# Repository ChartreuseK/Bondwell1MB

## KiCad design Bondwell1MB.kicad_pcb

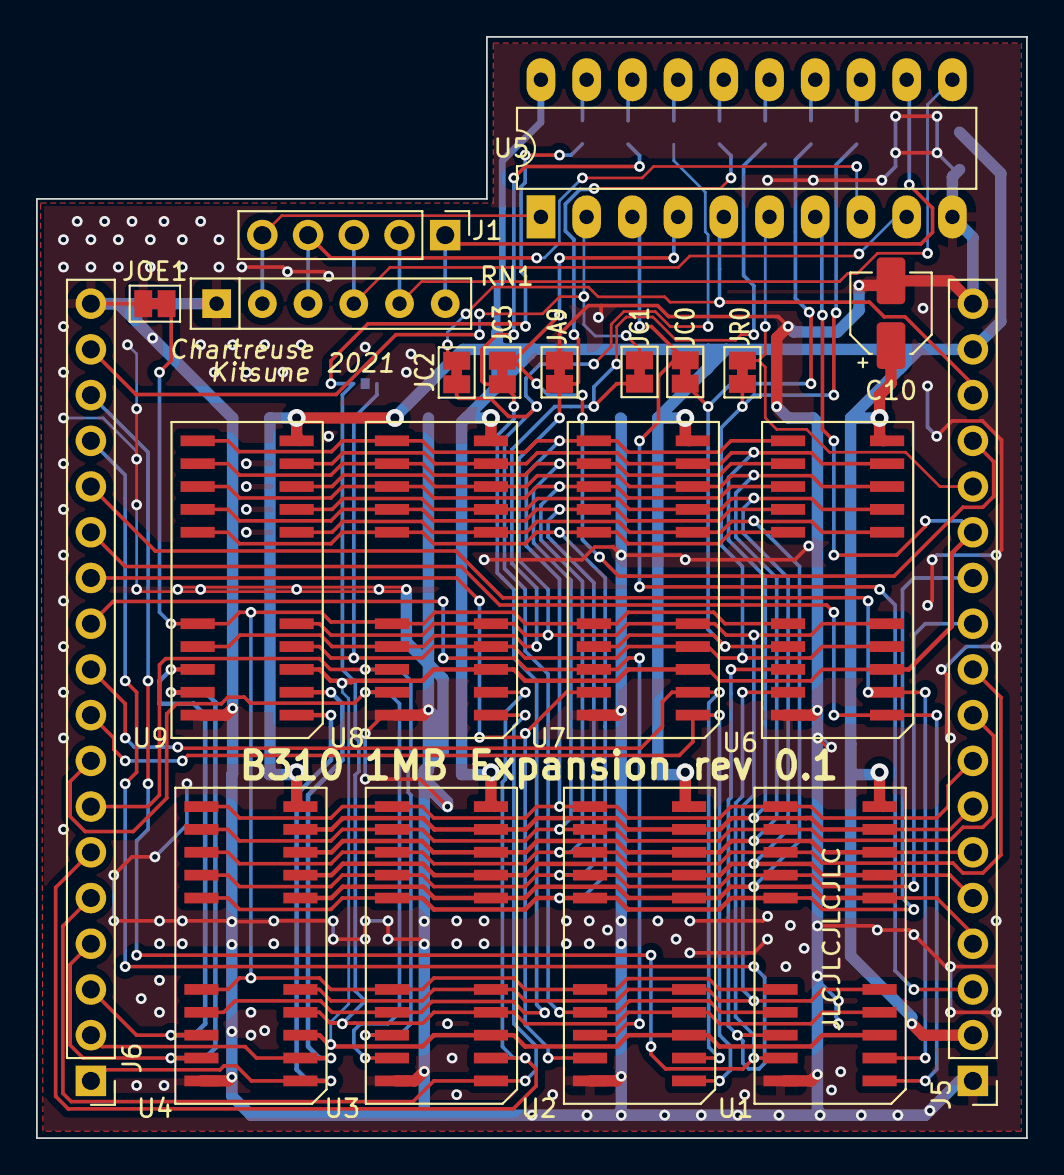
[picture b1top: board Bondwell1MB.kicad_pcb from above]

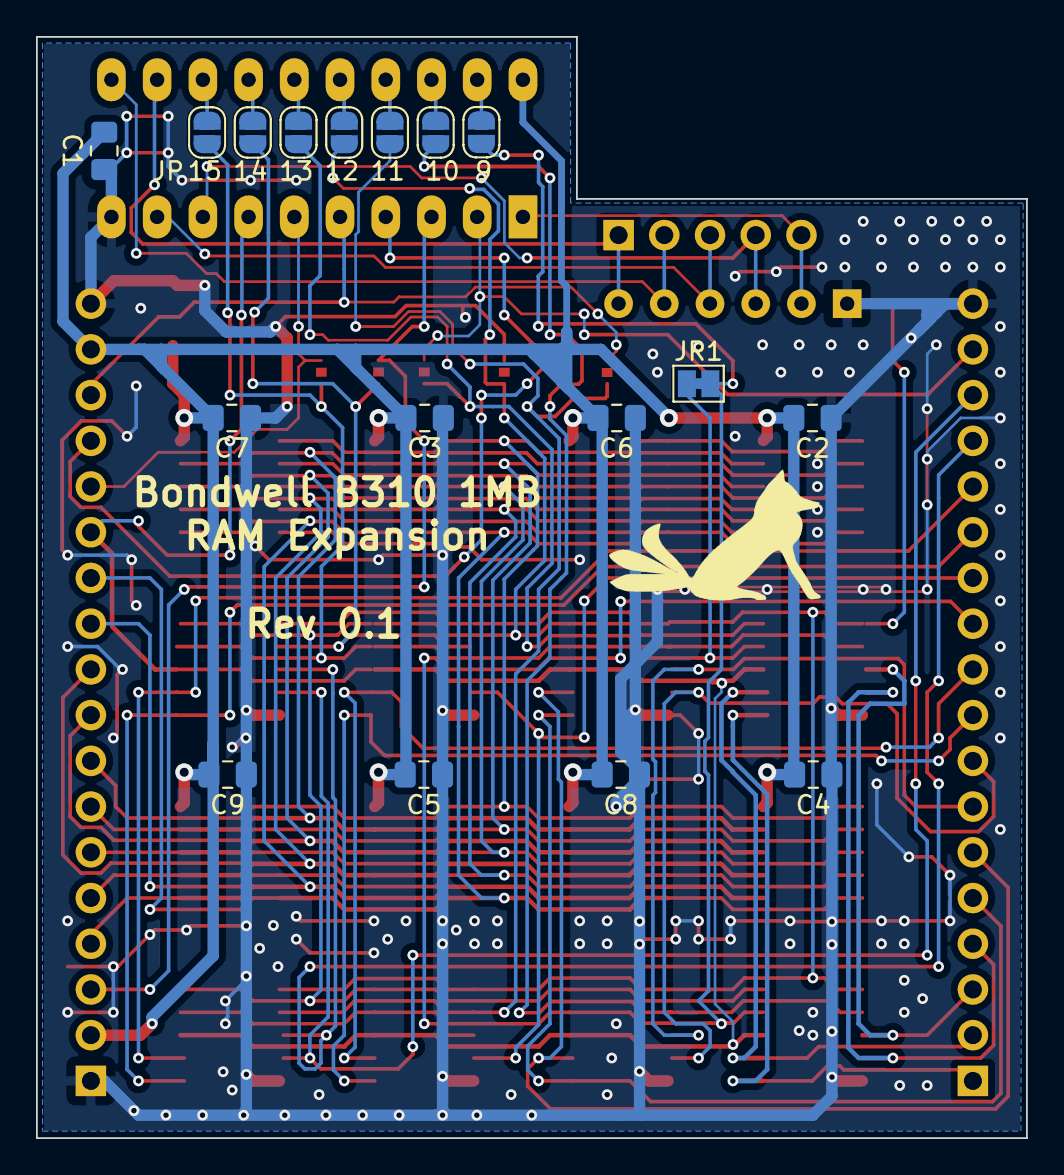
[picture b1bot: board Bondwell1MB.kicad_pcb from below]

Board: 2 copper layers, 55.0 x 61.2 mm, 38 parts (17 on the bottom side), 53 nets.

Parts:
9, 10, 11, 12, 13, 14, 15: SolderJumper_2_Open; SolderJumper-2_P1.3mm_Open_RoundedPad1.0x1.5mm
C1, C2, C3, C4, C5, C6, C7, C8, C9: 0.1uF; C_0805_2012Metric_Pad1.18x1.45mm_HandSolder
C10: 22uF 16v; CP_Elec_4x4.5
J1: Conn_01x05; PinHeader_1x05_P2.54mm_Vertical
J5, J6: Conn_01x18; PinHeader_1x18_P2.54mm_Vertical
JA9: SolderJumper_2_Bridged; SolderJumper-2_P1.3mm_Bridged_Pad1.0x1.5mm
JC0, JC1, JC2, JC3: SolderJumper_2_Bridged; SolderJumper-2_P1.3mm_Bridged_Pad1.0x1.5mm
JOE1: SolderJumper_2_Bridged; SolderJumper-2_P1.3mm_Bridged_Pad1.0x1.5mm
JR0, JR1: SolderJumper_2_Bridged; SolderJumper-2_P1.3mm_Bridged_Pad1.0x1.5mm
RN1: 10k; R_Array_SIP6
U1, U2, U3, U4, U6, U7, U8, U9: LH604256K-80A; SOJ-20_26
U5: GAL16V8; DIP-20_W7.62mm_LongPads

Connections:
/A0: J5.4, U1.9 (A0), U2.9 (A0), U3.9 (A0), U4.9 (A0), U6.9 (A0), U7.9 (A0), U8.9 (A0), U9.9 (A0)
/A1: J5.5, U1.10 (A1), U2.10 (A1), U3.10 (A1), U4.10 (A1), U6.10 (A1), U7.10 (A1), U8.10 (A1), U9.10 (A1)
/A2: J5.6, U1.11 (A2), U2.11 (A2), U3.11 (A2), U4.11 (A2), U6.11 (A2), U7.11 (A2), U8.11 (A2), U9.11 (A2)
/A3: J5.7, U1.12 (A3), U2.12 (A3), U3.12 (A3), U4.12 (A3), U6.12 (A3), U7.12 (A3), U8.12 (A3), U9.12 (A3)
/A4: J5.8, U1.14 (A4), U2.14 (A4), U3.14 (A4), U4.14 (A4), U6.14 (A4), U7.14 (A4), U8.14 (A4), U9.14 (A4)
/A5: J5.9, U1.15 (A5), U2.15 (A5), U3.15 (A5), U4.15 (A5), U6.15 (A5), U7.15 (A5), U8.15 (A5), U9.15 (A5)
/A6: J5.10, U1.16 (A6), U2.16 (A6), U3.16 (A6), U4.16 (A6), U6.16 (A6), U7.16 (A6), U8.16 (A6), U9.16 (A6)
/A7: J5.11, U1.17 (A7), U2.17 (A7), U3.17 (A7), U4.17 (A7), U6.17 (A7), U7.17 (A7), U8.17 (A7), U9.17 (A7)
/A8: J5.12, U1.18 (A8), U2.18 (A8), U3.18 (A8), U4.18 (A8), U6.18 (A8), U7.18 (A8), U8.18 (A8), U9.18 (A8)
/A9: 12.2, JA9.2 (B), U1.5 (NC/A9), U2.5 (NC/A9), U3.5 (NC/A9), U4.5 (NC/A9), U6.5 (NC/A9), U7.5 (NC/A9), U8.5 (NC/A9), U9.5 (NC/A9)
/D0_IC1: J6.13, U1.1 (D0), U6.1 (D0)
/D0_IC2: J6.9, U2.1 (D0), U7.1 (D0)
/D0_IC3: J6.5, U3.1 (D0), U8.1 (D0)
/D0_IC4: J6.1, U4.1 (D0), U9.1 (D0)
/D1_IC1: J6.14, U1.2 (D1), U6.2 (D1)
/D1_IC2: J6.10, U2.2 (D1), U7.2 (D1)
/D1_IC3: J6.6, U3.2 (D1), U8.2 (D1)
/D1_IC4: J6.2, U4.2 (D1), U9.2 (D1)
/D2_IC1: J6.15, U1.24 (D2), U6.24 (D2)
/D2_IC2: J6.11, U2.24 (D2), U7.24 (D2)
/D2_IC3: J6.7, U3.24 (D2), U8.24 (D2)
/D2_IC4: J6.3, U4.24 (D2), U9.24 (D2)
/D3_IC1: J6.16, U1.25 (D3), U6.25 (D3)
/D3_IC2: J6.12, U2.25 (D3), U7.25 (D3)
/D3_IC3: J6.8, U3.25 (D3), U8.25 (D3)
/D3_IC4: J6.4, U4.25 (D3), U9.25 (D3)
/~B_CAS0: J5.3, JC0.1 (A), U5.3 (I3)
/~B_CAS1: J6.17, JC1.1 (A), U5.2 (I2)
/~B_CAS2: J5.16, JC2.1 (A), U5.5 (I5)
/~B_CAS3: J5.15, JC3.1 (A), U5.4 (I4)
/~B_RAS: J5.14, JR0.1 (A), U5.6 (I6)
/~CAS0: 14.2, JC0.2 (B), U6.23 (~CAS), U7.23 (~CAS)
/~CAS1: 13.2, JC1.2 (B), U8.23 (~CAS), U9.23 (~CAS)
/~CAS2: 11.2, JC2.2 (B), U1.23 (~CAS), U2.23 (~CAS)
/~CAS3: 10.2, JC3.2 (B), U3.23 (~CAS), U4.23 (~CAS)
/~OE: JOE1.2 (B), U1.22 (~OE), U2.22 (~OE), U3.22 (~OE), U4.22 (~OE), U6.22 (~OE), U7.22 (~OE), U8.22 (~OE), U9.22 (~OE)
/~RAS0: 15.2, JR0.2 (B), JR1.1 (A), U6.4 (~RAS), U7.4 (~RAS), U8.4 (~RAS), U9.4 (~RAS)
/~RAS1: 9.2, JR1.2 (B), U1.4 (~RAS), U2.4 (~RAS), U3.4 (~RAS), U4.4 (~RAS)
/~WE: J5.13, U1.3 (~WE), U2.3 (~WE), U3.3 (~WE), U4.3 (~WE), U5.7 (I7), U6.3 (~WE), U7.3 (~WE), U8.3 (~WE), U9.3 (~WE)
GND: C1.1, C2.1, C3.1, C4.1, C5.1, C6.1, C7.1, C8.1, C9.1, C10.2, J5.1, J5.18, J6.18, JA9.1 (A), JOE1.1 (A), RN1.1 (common), U1.26 (Vss), U2.26 (Vss), U3.26 (Vss), U4.26 (Vss), U5.10 (GND), U6.26 (Vss), U7.26 (Vss), U8.26 (Vss), U9.26 (Vss)
unnamed: J1.1, RN1.6 (R5), U5.12 (IO8)
unnamed: J1.2, RN1.5 (R4), U5.11 (I10/~OE)
unnamed: J1.3, RN1.4 (R3), U5.9 (I9)
unnamed: J1.4, RN1.3 (R2), U5.8 (I8)
unnamed: J1.5, RN1.2 (R1), U5.1 (I1/CLK)
unnamed: 9.1, U5.19 (IO1)
unnamed: 10.1, U5.18 (IO2)
unnamed: 11.1, U5.17 (I03)
unnamed: 12.1, U5.16 (IO4)
unnamed: 13.1, U5.15 (IO5)
unnamed: 14.1, U5.14 (IO6)
unnamed: 15.1, U5.13 (IO7)
VCC: C1.2, C2.2, C3.2, C4.2, C5.2, C6.2, C7.2, C8.2, C9.2, C10.1, J5.2, J5.17, U1.13 (Vcc), U2.13 (Vcc), U3.13 (Vcc), U4.13 (Vcc), U5.20 (VCC), U6.13 (Vcc), U7.13 (Vcc), U8.13 (Vcc), U9.13 (Vcc)

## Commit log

2022-01-31 Added BSD license (To be determined if best for hardware schematics)
2022-01-31 Added PDF of schematic for easy viewing
